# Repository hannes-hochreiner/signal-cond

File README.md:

# signal-cond
A simple signal conditioning circuit based on a [TI application note by Pete Wilson](http://www.ti.com/lit/an/sboa096/sboa096.pdf).

The circuit performs a linear transform of the voltage range from +/-30V to 0-3V.
I designed this circuit to safely use piezo-electric transducer that was specified for the range of -30 to +30V.

The board and the parts can be ordered from [AISLER](http://aisler.net/p/DYDJTZVP).

The scaling factor of the circuit can be modified by changing the ratio of R1/R3 and R2/R4.
The offset can be set by changing Vref, which is dependent on the ratio of R7/R8.

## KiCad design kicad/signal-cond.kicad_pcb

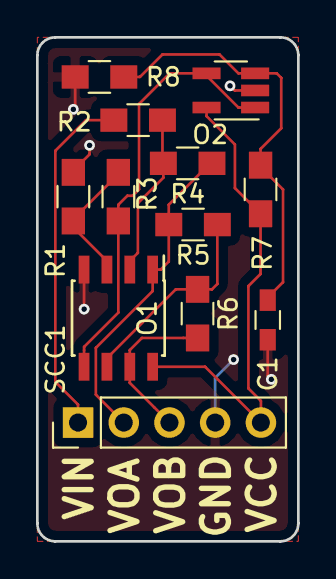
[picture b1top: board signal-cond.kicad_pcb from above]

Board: 2 copper layers, 14.5 x 28.0 mm, 12 parts (0 on the bottom side), 10 nets.

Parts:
C1: 0.1µF; R_0603_HandSoldering
O1: TI-OPA2301-SO-8; SOIC-8_3.9x4.9mm_Pitch1.27mm
O2: TI-OPA335-SOT23-5; SOT-23-5_HandSoldering
R1, R2: 20k; R_0805_HandSoldering
R3, R4: 1k; R_0805_HandSoldering
R5, R6, R7, R8: 10k; R_0805_HandSoldering
SCC1: SIGNAL-COND-CONNECTOR; Pin_Header_Straight_1x05_Pitch2.54mm

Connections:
/VOUTA: O1.1, R4.1, R5.2, SCC1.2
/VOUTB: O1.7, R6.2, SCC1.3
/VREF: O1.5, O2.1, O2.4, R3.2
GND: C1.2, O1.4, O2.2, R1.2, R8.2, SCC1.4
unnamed: C1.1, O2.3, R7.2, R8.1
unnamed: O1.2, R2.1, R4.2
unnamed: O1.3, R1.1, R3.1
unnamed: O1.6, R5.1, R6.1
unnamed: R2.2, SCC1.1
VCC: O1.8, O2.5, R7.1, SCC1.5

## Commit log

2017-08-06 added simulation, circuit, and board
2017-08-06 added bom
2017-08-06 improved routing
2017-08-19 added image and expanded readme
